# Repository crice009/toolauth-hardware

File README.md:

# toolauth-hardware
The custom PCB for the toolauth system. Intended to control access to tools (based on credentials) in a shared workshop. Designed to work with an ESP32 board and ESPHome.

Completely designed in KiCAD 6 and ordered as assembled boards from JLCPCB.

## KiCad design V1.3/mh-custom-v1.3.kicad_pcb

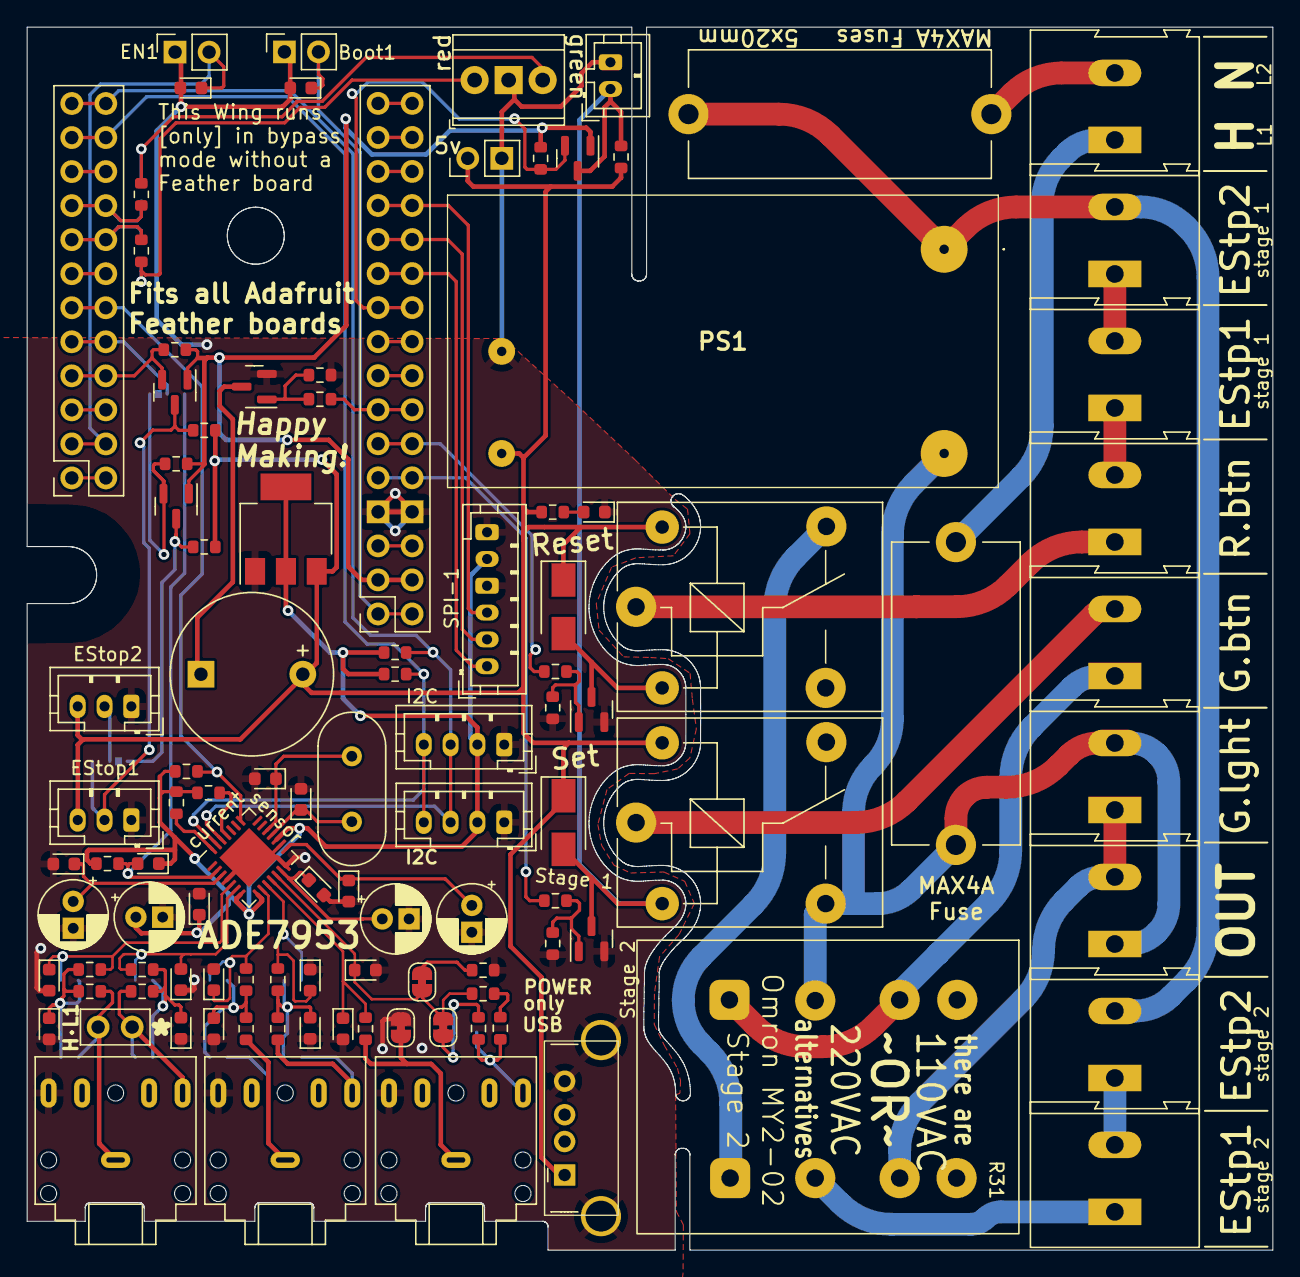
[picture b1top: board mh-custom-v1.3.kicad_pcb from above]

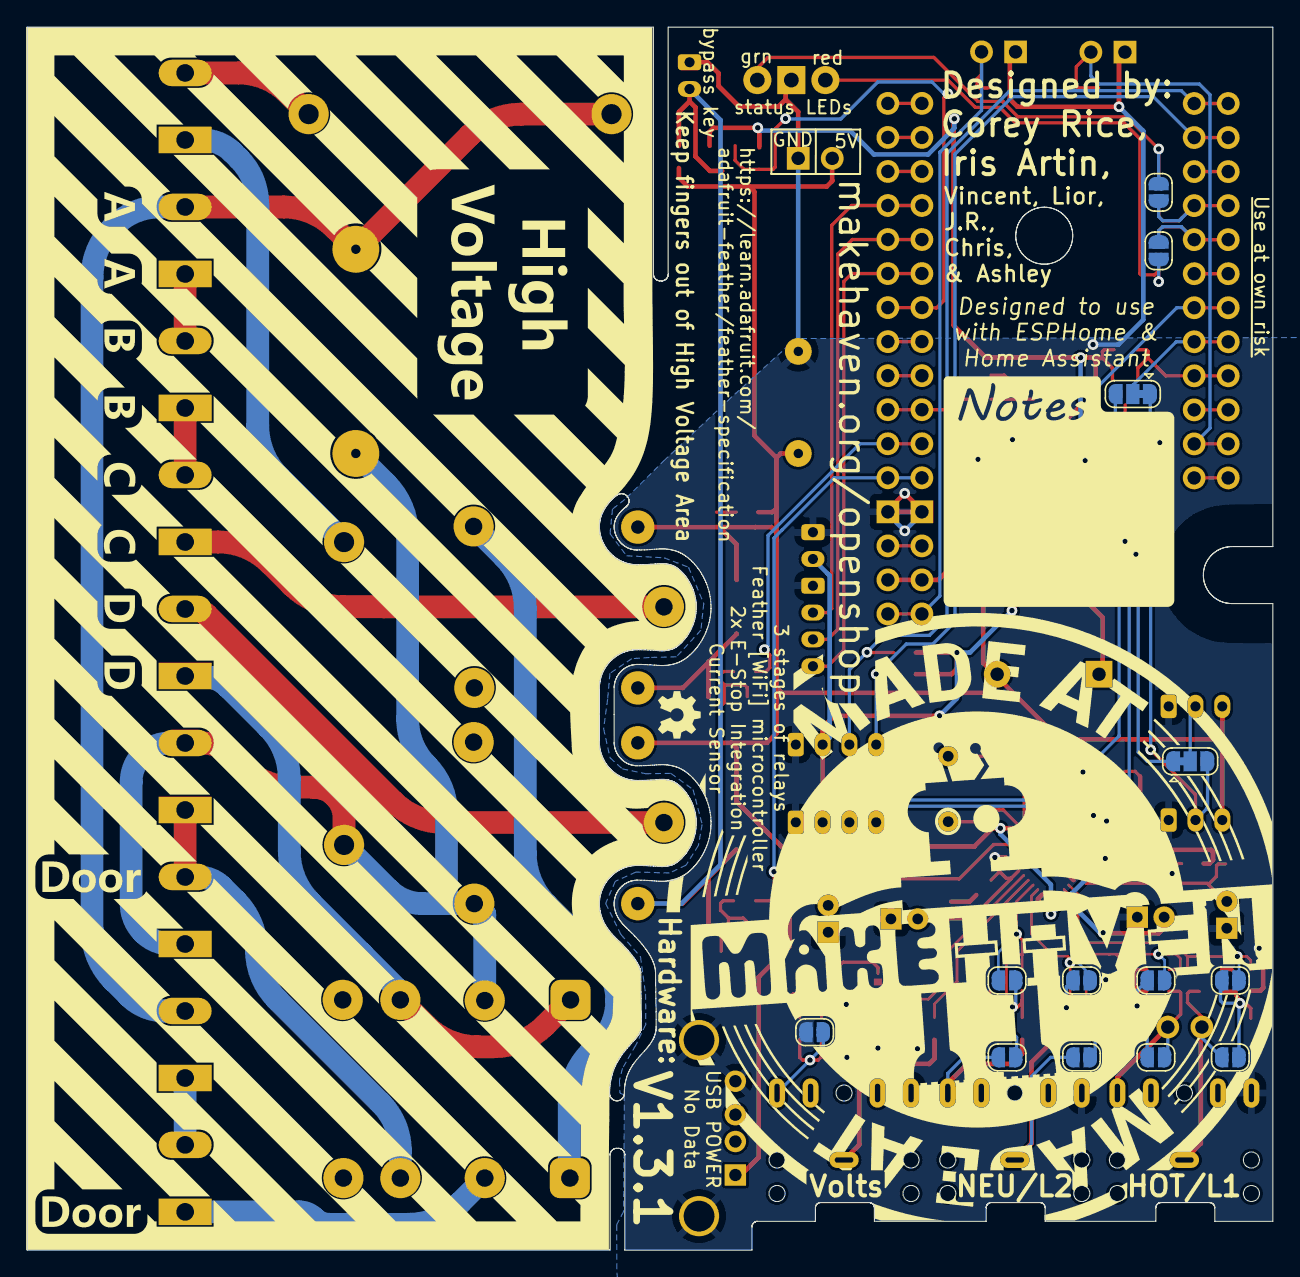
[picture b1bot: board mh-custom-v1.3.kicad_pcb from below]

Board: 2 copper layers, 93.0 x 91.3 mm, 118 parts (13 on the bottom side), 83 nets.

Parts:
BZ1: Buzzer; Buzzer_12x9.5RM7.6
Boot1: Conn_01x02_Female; PinSocket_1x02_P2.54mm_Vertical
Bypass-1: Conn_01x02_Female; JST_PH_B2B-PH-K_1x02_P2.00mm_Vertical
C1, C2: 0.1uF; LED_0603_1608Metric
C3, C4, C5, C6, C7, C8, C9, C10, C11, C12: 33nF; LED_0603_1608Metric
C13, C16, C17, C22: 100nF; LED_0603_1608Metric
C14: 10uF; CP_Radial_D5.0mm_P2.00mm
C15: 1uF; LED_0603_1608Metric
C18, C19, C23: 4.7uF; CP_Radial_D5.0mm_P2.00mm
C20, C21: 20pF; LED_0603_1608Metric
D2: LED; LED_0603_1608Metric
D3, D4: B160-E3; D_SMA
EN1: Conn_01x02_Female; PinSocket_1x02_P2.54mm_Vertical
EStop1, EStop2: Conn_01x03_Female; JST_PH_B3B-PH-K_1x03_P2.00mm_Vertical
F1, F2: Fuse; Fuseholder_Cylinder-5x20mm_Stelvio-Kontek_PTF78_Horizontal_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
I2C-2, I2C-3: Conn_01x04_Female; JST_PH_B4B-PH-K_1x04_P2.00mm_Vertical
IN-1, IN-2, IN-3: 3.5mm; Jack_3.5mm_CUI_SJ1-3525N_Horizontal
IN-AUX-1: H/L1; PinHeader_1x02_P2.54mm_Vertical
J1: Conn_01x03_Male; TerminalBlock_TE_282834-3_1x03_P2.54mm_Horizontal
J5, J6, J7, J8, J9, J10, J11, J12, J14: Screw_Terminal_01x02; TerminalBlock_Altech_AK300-2_P5.00mm
J13: USB_A; USB_A_Stewart_SS-52100-001_Horizontal
J15: Conn_02x16_Row_Letter_Last; PinSocket_2x16_P2.54mm_Vertical
J16: Conn_02x12_Row_Letter_Last; PinSocket_2x12_P2.54mm_Vertical
JP1, JP2, JP3, JP4, JP5, JP8, JP9, JP10, JP11, JP15, JP16: no-filter-1; SolderJumper-2_P1.3mm_Open_RoundedPad1.0x1.5mm
JP6, JP7, JP12: bridged; SolderJumper-2_P1.3mm_Bridged_RoundedPad1.0x1.5mm
JP13, JP14: SolderJumper_3_Bridged12; SolderJumper-3_P1.3mm_Bridged12_RoundedPad1.0x1.5mm
PS1: CFM06S050; CFM06S050E
R1, R5, R6, R14, R15, R16, R17, R18, R20, R21, R26, R27, R29: 1k; R_0603_1608Metric
R2, R3, R4, R22, R23, R24, R25, R28, R30, R32, R33, R34, R35: 10k; R_0603_1608Metric
R7, R8: 2.2k; R_0603_1608Metric
R9, R10, R11, R12: 100; R_0603_1608Metric
R13, R19: 499k; R_0603_1608Metric
R31: Relay_Omron_MY2-02; relay-Omron-MY2-02
SPI-1: Conn_01x06_Female; JST_PH_B6B-PH-K_1x06_P2.00mm_Vertical
T1, T2, T3, T4, T5, T6: AO3400A; SOT-23
U2: ADE7953xCP; LFCSP-28-1EP_5x5mm_P0.5mm_EP3.14x3.14mm
U3: AMS1117-3.3; SOT-223-3_TabPin2
Y1: 3.58MHz; Crystal_HC49-4H_Vertical
pwr5v1: extra; PinHeader_1x02_P2.54mm_Vertical
relay1, relay2: JQC-3FF/005-1ZS(551); Relay_SPDT_SANYOU_SRD_Series_Form_C

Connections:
3vRead-Bypass: J15.19, J15.20, R32.1, T5.2 (S)
+3.3V: C13.1, C14.1, C15.1, I2C-2.2, I2C-3.2, R7.2, R8.2, R22.2, R23.2, R24.2, R25.2, SPI-1.5, U2.7 (PULL_HIGH), U2.8 (PULL_HIGH), U2.17 (VDD), U3.2 (VO)
+3.3VA: J15.3, J15.4, R3.2, R32.2, R34.2, T2.1 (G), T5.1 (G), T6.1 (G)
+5V: BZ1.1 (-), D3.1 (K), D4.1 (K), EStop1.3, EStop2.3, J13.1 (VBUS), PS1.3 (+VOUT), R4.2, R26.2, R33.2, R35.2, U3.3 (VI), pwr5v1.1, relay1.5, relay2.5
/mainslevelcontrol/stage1relays/dcp2: D4.2 (A), T4.3 (D), relay2.2
/microcontroller/lightsounds/dcp1: BZ1.2 (+), T1.3 (D)
CS: R24.1, U2.28 (~CS)
EN: C2.1, EN1.2, J16.3, J16.4
GND: Boot1.1, Bypass-1.2, C1.2, C2.2, C3.2, C4.1, C5.2, C6.1, C7.2, C8.1, C9.2, C10.1, C11.2, C12.2, C13.2, C14.2, C16.2, C17.2, C18.2, C19.2, C20.2, C21.2, C22.2, C23.2, D2.1 (K), EN1.1, EStop1.1, EStop2.1, I2C-2.1, I2C-3.1, IN-1.R, IN-2.R, IN-3.R, J1.2, J13.4 (GND), J13.5 (Shield), J15.7, J15.8, JP1.1 (A), JP6.1 (A), PS1.4 (-VOUT), R2.1, R21.2, R28.2, R30.2, SPI-1.4, SPI-1.6, T1.2 (S), T3.2 (S), T4.2 (S), U2.4 (DGND), U2.14 (PULL_LOW), U2.16 (AGND), U2.29 (EP), U3.1 (GND), pwr5v1.2
Green-Indicator-light-1: F1.2, J12.2, J14.1, PS1.2 (ACL), R31.9, relay1.3
Green-Indicator-light-2: J12.1, J14.2, R31.8
H/L1: F1.1, J5.1
IAN: C8.2, JP9.1 (A), R16.1, U2.6 (IAN)
IAN_IN: IN-1.T, IN-AUX-1.2, JP3.2 (B), R10.2
IAP: C7.1, JP8.2 (B), R15.2, U2.5 (IAP)
IAP_IN: IN-1.S, IN-AUX-1.1, JP2.1 (A), R9.1
IBN: C10.2, JP11.1 (A), R18.1, U2.10 (IBN)
IBN_IN: IN-2.T, JP5.2 (B), R12.2
IBP: C9.1, JP10.2 (B), R17.2, U2.9 (IBP)
IBP_IN: IN-2.S, JP4.1 (A), R11.1
Member-E-Stop-aux1-1: J10.1, J11.2
Member-E-Stop-aux2-1: J8.2, J9.1
Member-E-Stop-aux2-2: F2.2, J9.2, J10.2, PS1.1 (ACN)
Member-E-Stop-sw1-1: J11.1, R31.12
Member-E-Stop-sw2-1: J7.2, J8.1
Member-Green-Button-1: J6.2, relay1.1
Member-Green-Button-2: J6.1, R31.5, R31.13
Member-Red-Reset-Button-1: J7.1, relay2.1
unnamed: D2.2 (A), R26.1
unnamed: EStop1.2, JP14.3 (B), R4.1, T2.3 (D)
unnamed: EStop2.2, JP14.2 (C)
unnamed: J1.1, JP16.2 (B), R6.1
unnamed: J1.3, JP15.2 (B), R5.2
unnamed: J15.5, J15.6
unnamed: J15.15, J15.16
unnamed: J15.17, J15.18
unnamed: J15.27, J15.28
unnamed: J15.29, J15.30
unnamed: J15.31, J15.32
unnamed: J16.1, J16.2
unnamed: J16.5, J16.6
unnamed: J16.13, J16.14
unnamed: J16.19, J16.20
unnamed: C3.1, JP2.2 (B), JP8.1 (A), R9.2, R15.1
unnamed: C4.2, JP3.1 (A), JP9.2 (B), R10.1, R16.2
unnamed: JP7.1 (A), R14.1
unnamed: C5.1, JP4.2 (B), JP10.1 (A), R11.2, R17.1
unnamed: C6.2, JP5.1 (A), JP11.2 (B), R12.1, R18.2
unnamed: JP12.1 (A), R21.1
unnamed: C15.2, JP13.3 (B), R22.1, U2.2 (~RESET)
unnamed: JP14.1 (A), R35.1, T6.3 (D)
unnamed: R13.1, R19.2
unnamed: R1.2, R2.2, T1.1 (G)
unnamed: R27.2, R28.1, T3.1 (G)
unnamed: R29.2, R30.1, T4.1 (G)
unnamed: C21.1, U2.18 (CLKIN), Y1.1
unnamed: C20.1, U2.19 (CLKOUT), Y1.2
unnamed: C22.1, C23.1, U2.13 (REF)
unnamed: C17.1, C19.1, U2.15 (VINTA)
unnamed: C16.1, C18.1, U2.3 (VINTD)
N/L2: F2.1, J5.2
PICO: J15.25, J15.26, SPI-1.3
POCI: J15.23, J15.24, SPI-1.2
SCK: J15.21, J15.22, SPI-1.1
SCL: I2C-2.4, I2C-3.4, J16.21, J16.22, R8.1, U2.27 (MOSI/SCL/RX)
SCLK: R25.1, U2.25 (SCLK)
SDA: I2C-2.3, I2C-3.3, J16.23, J16.24, R7.1, U2.26 (MISO/SDA/TX)
VN: C12.1, R20.1, U2.11 (VN)
VN_IN: IN-3.S, JP6.2 (B), R20.2
VP: C11.1, JP7.2 (B), JP12.2 (B), R19.1, U2.12 (VP)
VP_IN: IN-3.T, JP1.2 (B), R13.2, R14.2
ade7953-IRQ: J16.11, J16.12, R23.1, U2.22 (~IRQ)
boot: Boot1.2, C1.1, J15.1, J15.2
buzz: J15.13, J15.14, R1.1
led-grn: J16.15, J16.16, JP16.1 (A), R6.2
led-red: J16.17, J16.18, JP15.1 (A), R5.1
read-E-Stop: J16.7, J16.8, R3.1, T2.2 (S)
read-aux-E-Stop: JP13.1 (A), R34.1, T6.2 (S)
read-bypass: Bypass-1.1, D3.2 (A), R33.1, T3.3 (D), T5.3 (D), relay1.2
reset: R31.14, relay2.4
reset3v: J15.11, J15.12, R29.1
set3v: J15.9, J15.10, R27.1
two-options: J16.9, J16.10, JP13.2 (C)

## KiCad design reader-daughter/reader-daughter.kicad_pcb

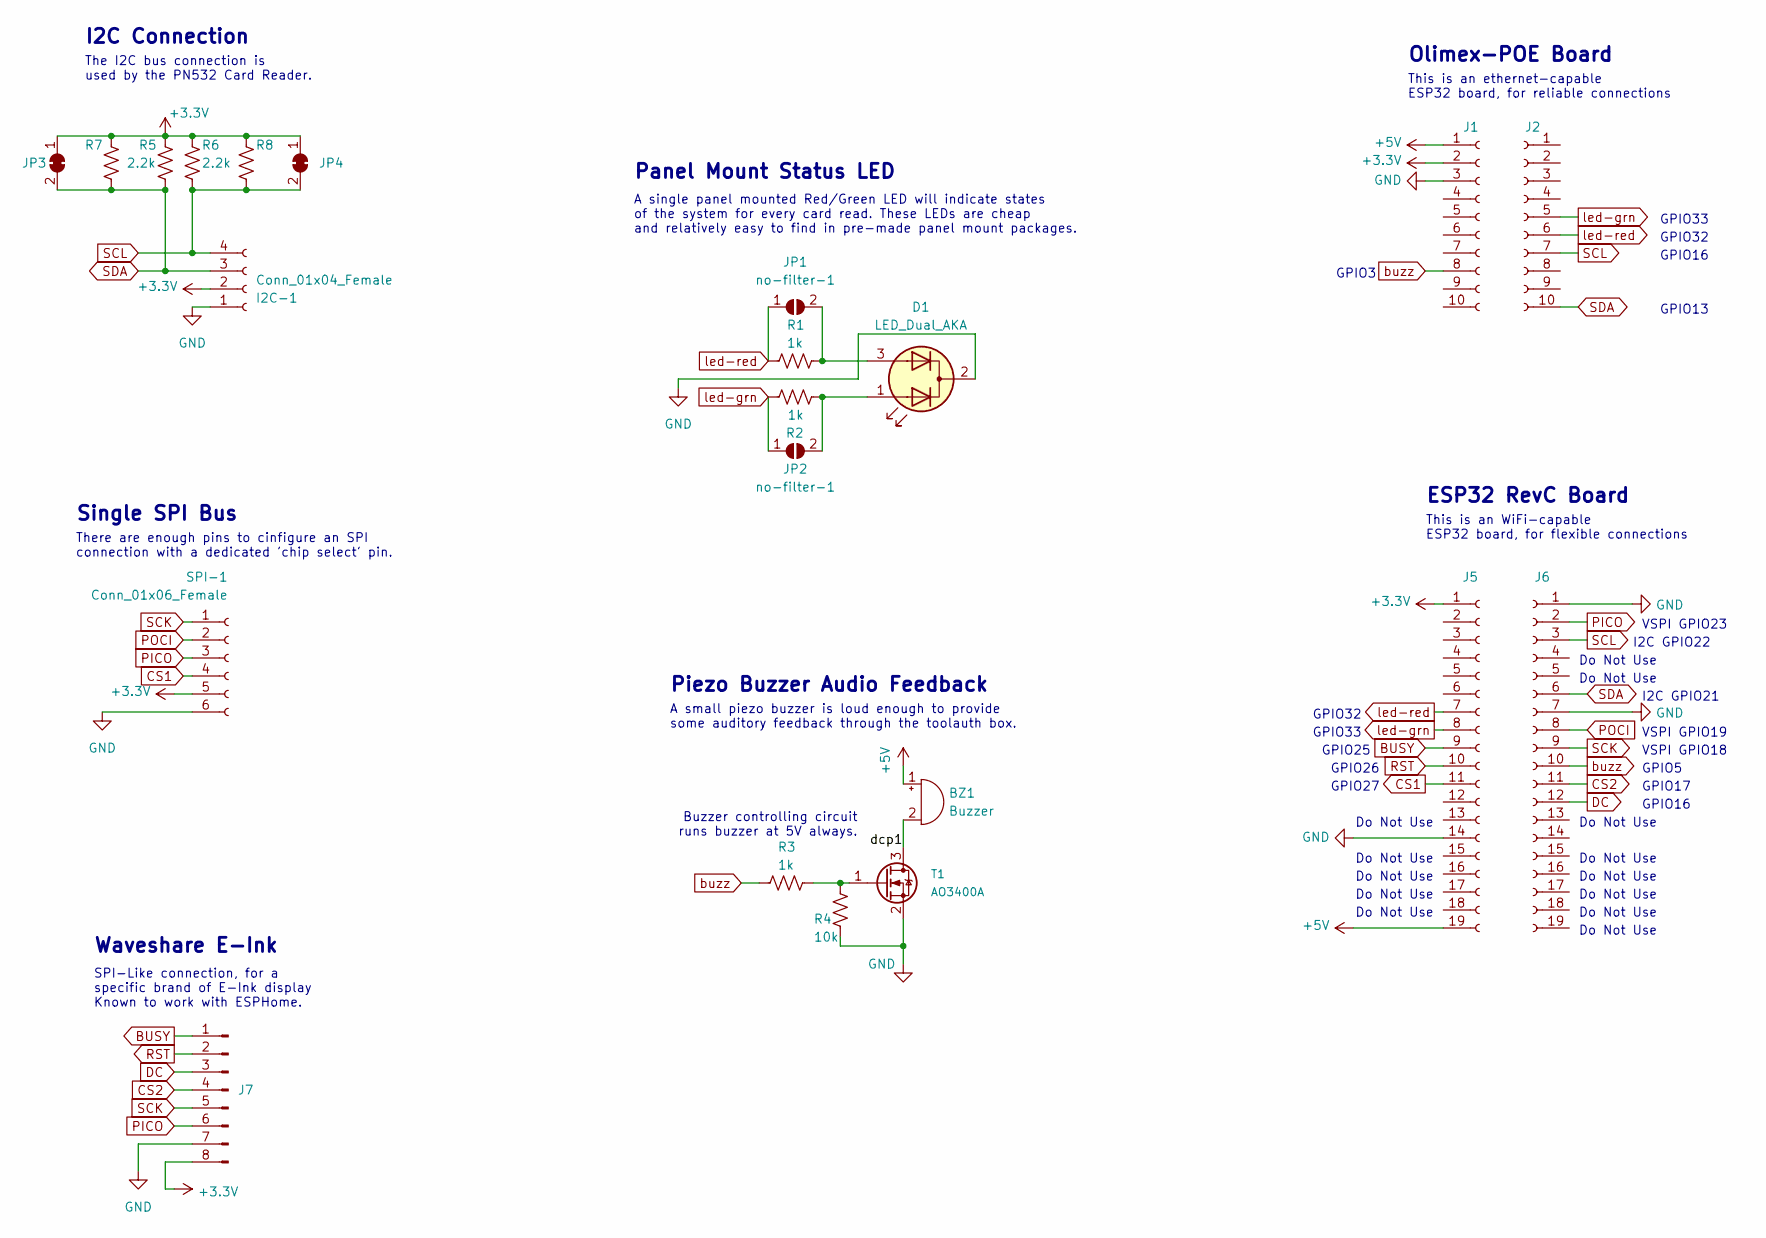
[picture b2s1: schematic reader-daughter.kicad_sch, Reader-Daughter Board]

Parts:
BZ1: Buzzer; Buzzer_12x9.5RM7.6; JLCPCB Part # C96095
D1: LED_Dual_AKA; LED_D5.0mm-3
I2C-1: Conn_01x04_Female; JST_PH_B4B-PH-K_1x04_P2.00mm_Vertical; JLCPCB Part # C131334
J1, J2: Conn_01x10_Female; PinSocket_1x10_P2.54mm_Vertical; JLCPCB Part # C2938384
J5, J6: Conn_01x19_Female; PinSocket_1x19_P2.54mm_Vertical; JLCPCB Part # C2906049
J7: Conn_01x08_Male; PinHeader_1x08_P2.54mm_Vertical
JP1, JP2: no-filter-1; SolderJumper-2_P1.3mm_Open_RoundedPad1.0x1.5mm
JP3, JP4: SolderJumper_2_Bridged; SolderJumper-2_P1.3mm_Bridged_RoundedPad1.0x1.5mm
R1, R2, R3: 1k; R_0603_1608Metric; JLCPCB Part # C21190
R4: 10k; R_0603_1608Metric; JLCPCB Part # C25804
R5, R6: 2.2k; R_0603_1608Metric; JLCPCB Part # C4190
R7, R8: 2.2k; R_Axial_DIN0207_L6.3mm_D2.5mm_P2.54mm_Vertical; JLCPCB Part # C4190
SPI-1: Conn_01x06_Female; JST_PH_B6B-PH-K_1x06_P2.00mm_Vertical; JLCPCB Part # C131342
T1: AO3400A; SOT-23; JLCPCB Part # C427382

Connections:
+3V3: I2C-1.2, J1.2, J5.1, J7.8, JP3.1 (A), JP4.1 (A), R5.2, R6.2, R7.2, R8.2, SPI-1.5
+5V: BZ1.1 (-), J1.1, J5.19
/dcp1: BZ1.2 (+), T1.3 (D)
BUSY: J5.9, J7.1
CS1: J5.11, SPI-1.4
CS2: J6.11, J7.4
DC: J6.12, J7.3
GND: D1.2 (K), I2C-1.1, J1.3, J5.14, J6.1, J6.7, J7.7, R4.1, SPI-1.6, T1.2 (S); also elsewhere on the board
unnamed: D1.3 (A2), JP1.2 (B), R1.2
unnamed: D1.1 (A1), JP2.2 (B), R2.1
unnamed: R3.2, R4.2, T1.1 (G)
PICO: J6.2, J7.6, SPI-1.3
POCI: J6.8, SPI-1.2
RST: J5.10, J7.2
SCK: J6.9, J7.5, SPI-1.1
SCL: I2C-1.4, J2.7, J6.3, JP4.2 (B), R6.1, R8.1
SDA: I2C-1.3, J2.10, J6.6, JP3.2 (B), R5.1, R7.1
buzz: J1.8, J6.10, R3.1
led-grn: J2.5, J5.8, JP2.1 (A), R2.2
led-red: J2.6, J5.7, JP1.1 (A), R1.1

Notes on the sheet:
Do Not Use
GPIO5
VSPI GPIO19
A single panel mounted Red/Green LED will indicate states of the system for every card read. These LEDs are cheap and relatively easy to find in pre-made panel mount packages.
I2C GPIO21
VSPI GPIO18
GPIO33
This is an ethernet-capable ESP32 board, for reliable connections
GPIO17
Single SPI Bus
There are enough pins to cinfigure an SPI connection with a dedicated 'chip select' pin.
GPIO32
VSPI GPIO23
GPIO3
Piezo Buzzer Audio Feedback
Buzzer controlling circuit runs buzzer at 5V always.
ESP32 RevC Board
GPIO13
GPIO26
This is an WiFi-capable ESP32 board, for flexible connections
GPIO16
GPIO25
Panel Mount Status LED
Olimex-POE Board
I2C GPIO22
Waveshare E-Ink
The I2C bus connection is used by the PN532 Card Reader.
A small piezo buzzer is loud enough to provide some auditory feedback through the toolauth box.
I2C Connection
GPIO27
SPI-Like connection, for a specific brand of E-Ink display Known to work with ESPHome.

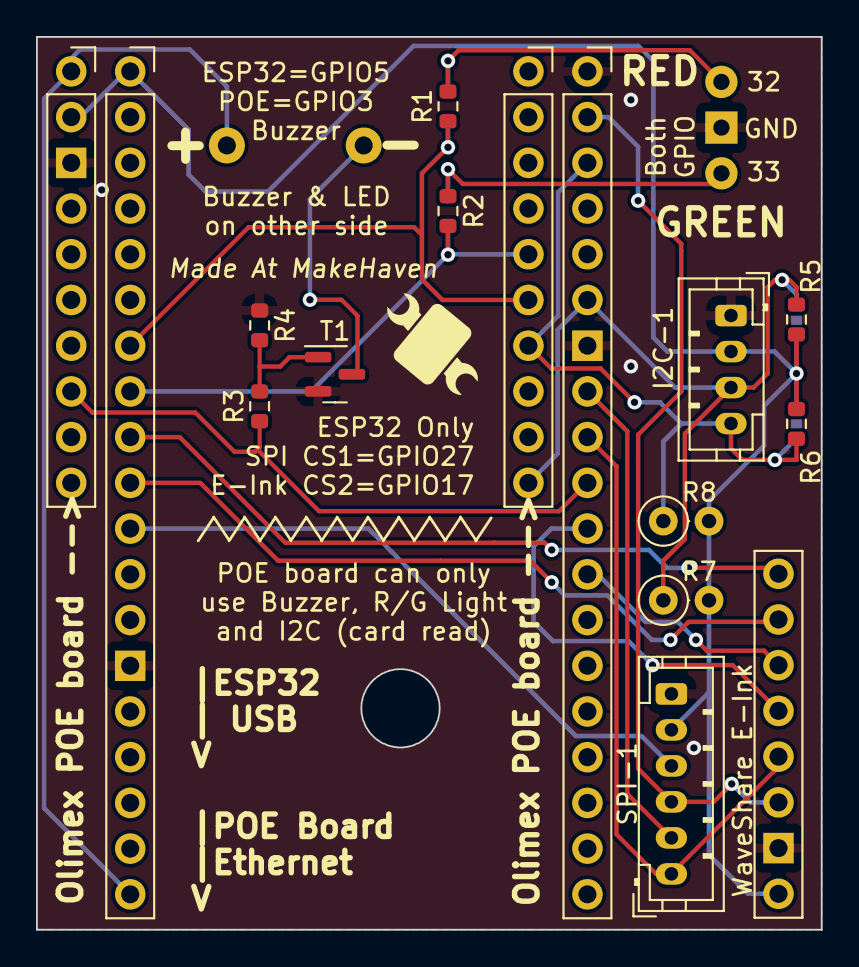
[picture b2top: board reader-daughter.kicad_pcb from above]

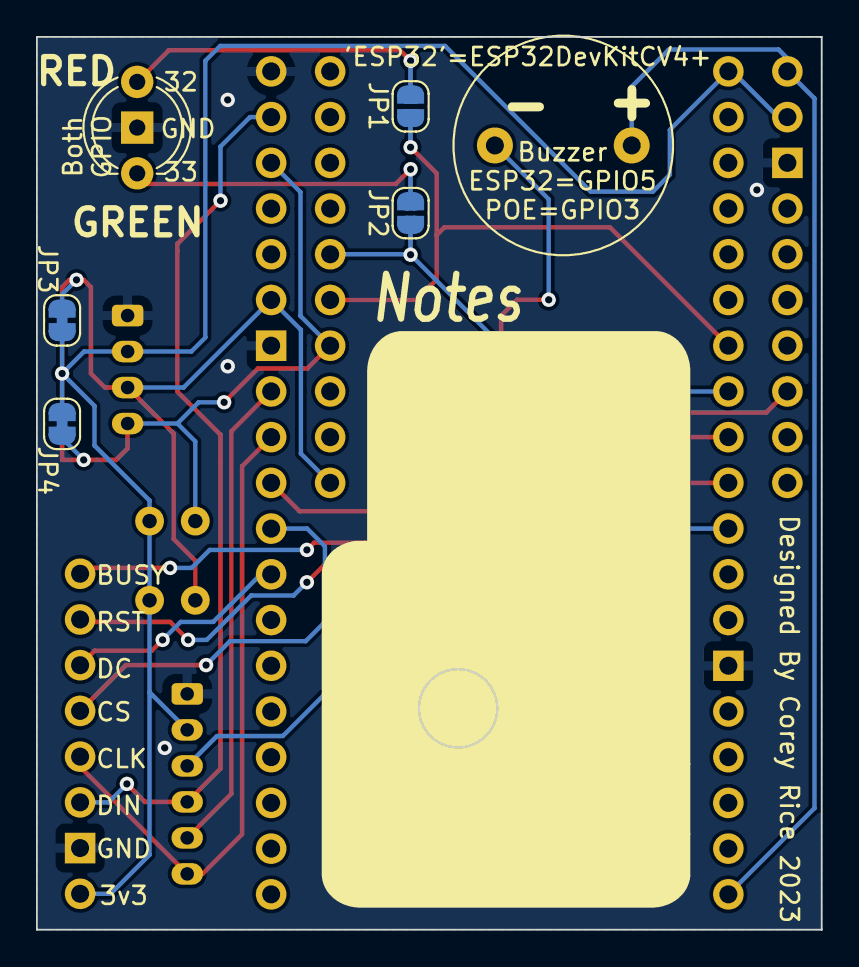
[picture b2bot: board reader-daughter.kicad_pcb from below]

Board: 2 copper layers, 43.6 x 49.6 mm, 22 parts (6 on the bottom side), 20 nets.

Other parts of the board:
J3: Conn_01x03_Male; LED_D5.0mm-3

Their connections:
GND: J3.2; also elsewhere on the board

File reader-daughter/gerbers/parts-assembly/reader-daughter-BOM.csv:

Comment,Designator,Footprint,JLCPCB Part #
Conn_01x04_Female,I2C-1,JST_PH_B4B-PH-K_1x04_P2.00mm_Vertical,C131334
1k,"R2,R3,R1",R_0603_1608Metric,C21190
Conn_01x06_Female,SPI-1,JST_PH_B6B-PH-K_1x06_P2.00mm_Vertical,C131342
Conn_01x10_Female,"J2,J1",PinSocket_1x10_P2.54mm_Vertical,C358723 
2.2k,"R6,R5",R_0603_1608Metric,C4190
Conn_01x19_Female,"J6,J5",PinSocket_1x19_P2.54mm_Vertical,C2897382 
AO3400A,T1,SOT-23,C427382
10k,R4,R_0603_1608Metric,C25804

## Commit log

2022-11-05 updated license to cover hardware & firmware
2022-11-05 design files added
2022-11-05 adding simplest firmware to test operation
2022-11-05 reorganized
2022-11-06 social logo added
2022-11-06 rerouted to save space
2022-11-06 jumpers added to bottom
2022-11-06 fixing edges and connecting all pieces
2022-11-07 connections made, style points added. needs double-check
2022-11-08 finished B silkscreen
2022-11-08 baby steps toward documentation
2022-11-08 minor adjustments F Silkscreen
2022-11-08 updated readme to include KiCAD
2022-11-19 updated logo, based on feedback
2022-11-24 logo
2022-12-02 added board renders to readme
2022-12-02 added board renders | edit
2023-01-07 added api services to test.
2023-01-27 fix(breakoutboards): flipped I2C pins, to conform with common wire colors [on JST connectors]
2023-02-01 close the last ratsnests
2023-02-28 clarify door-activator role || Active & Passive door operation
2023-03-09 fix(board): correct lables for the stage 1 relays
2023-03-09 fix(board): b.silkscreen updated to show connections for use as a door controller
2023-04-05 fix(lightsounds): add bypass jumpers for the resistors on the indicator LEDS --> in case there is an indicator with resistors baked-in
2023-07-18 added stage levels to Estops on F.Silkscreen
2023-07-18 made EStop Header labels more readable
2023-07-19 change silkscreen lables for the E-Stop JST connectors, to match large-gauge wiring
2023-07-19 added start of a documentaton page
2023-07-19 formatting fix
2023-07-19 added a few more comments at the end of docs
2023-07-27 added the reader-daughter board, from second order at JLCPCB
2023-07-27 start documentation for reader-daughter baord
2023-07-27 include the BOM files, from gitignore
2023-07-27 added reader-daugheter PDF schematic
2023-07-27 added schematic to documentation
2023-07-27 toolauth-hardware Schematic added
2023-07-27 added tool-controller schematic to documentation
2023-07-27 documentation to include schematics
2023-07-27 update v1.3 schematic documentation
2023-07-27 relink schematic to new version
2023-07-27 ensure gerbers are updated for reader-daughter board
2023-07-27 fixed gitignore to not include backups
2023-07-27 center docs pages
2023-07-27 added links to automationdirect.com buttons/lights
2023-07-28 spelling fixes
2023-07-29 tool controller page to include box link
2023-07-29 keepout zone changes
2023-07-29 redirect to new tab for all external links
2023-07-29 added logo PNG
2023-07-29 added box-layout .svg, and it's placement in the documentation.
2023-07-29 added 3D models for Reader-daughter holders
2023-07-30 fixes to board, based on Iris' feedback
2023-07-31 remade the 'made-at-makehaven' logo
2023-07-31 update images for new board version
2023-07-31 websafe fonts in SVG for Box Layout
2023-07-31 box layout SVG fonts didn't work: converted to paths
2023-07-31 box layout SVG layer fix
2023-08-03 fixed typo
2023-08-03 expanded index page
2023-08-03 style updates to docs pages
2023-08-03 lazy spacing break
2023-08-03 revise list styles
2023-08-03 spelling fix
2023-08-09 reader daughter documentation update
2023-08-09 reader daughter pictures
2023-08-09 font warning
2023-08-09 led clarity
2023-08-10 updated boards with improved silkscreen and pad-shapes
2023-08-10 changed images to fit with new board design
2023-08-10 missed one of the new images
2023-08-10 Inkscape design to make images
2023-08-10 updated reader-daughter page to reflect new images
2023-08-13 added note for jumperrs that need cut with ESP32 boards
2023-12-24 add photo documentation to help with wiring the b1p2 boards
2024-02-29 change to feather footprint for ESP32 driver board
2024-02-29 started adding the feather footprint to the board. need to update board shape and silkscreens
2024-03-01 design for feather-based board should work, but nothing is pretty
2024-03-01 updated USB to correct JLCPCB part #
2024-03-02 added revised silkscreen items
2024-03-02 moved bypass key and led labels
2024-03-02 rounded high voltage tracks
2024-03-02 revised some values for interactive BOM
2024-03-03 added interactive Bill of Materials
2024-03-03 some new images
2024-03-03 adjust silkscreen
